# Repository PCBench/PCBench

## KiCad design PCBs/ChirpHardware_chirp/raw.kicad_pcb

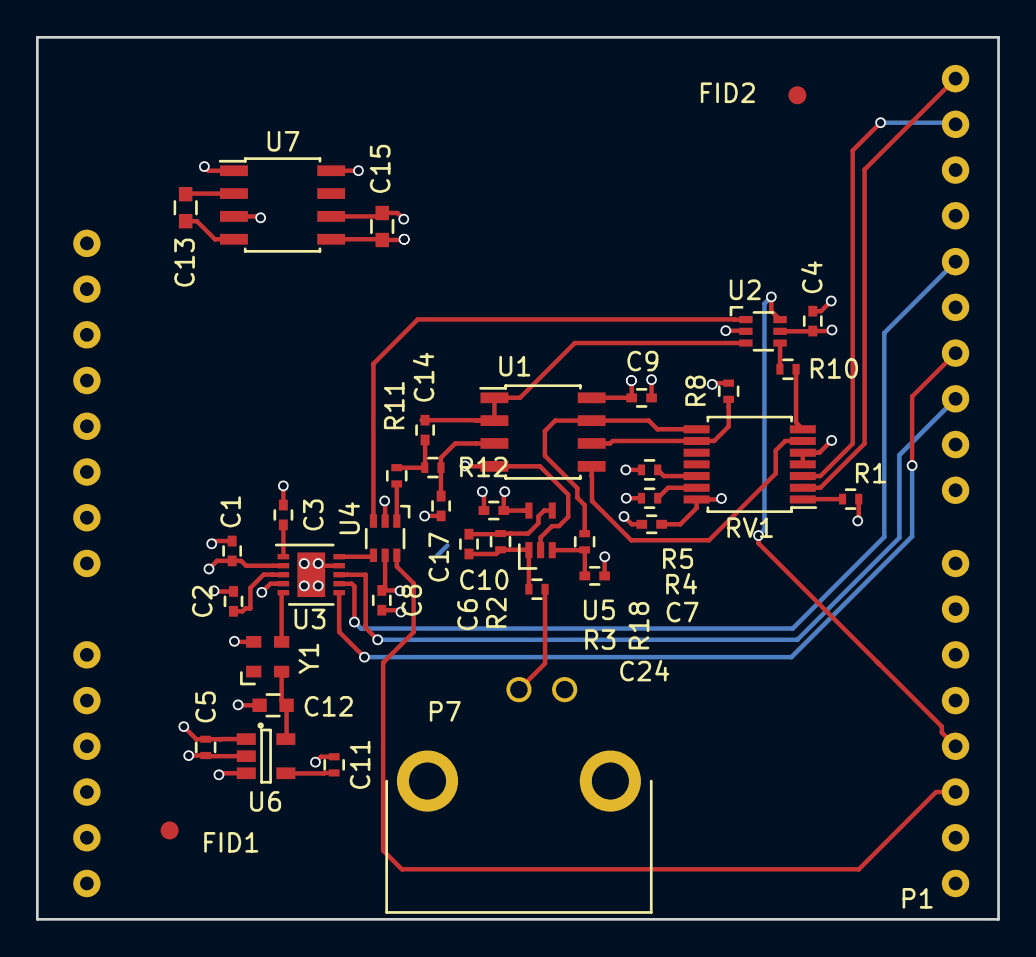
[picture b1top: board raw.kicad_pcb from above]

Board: 4 copper layers, 53.4 x 49.0 mm, 40 parts (0 on the bottom side), 35 nets.

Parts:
C1, C2, C3, C6, C14, C17, C24: C; C_0402
C4, C8, C9, C10: 0.01uF; C_0402
C5: 1uF; R_0402
C7: 0.1uF; C_0402
C11: 10nF; R_0402
C12: 2.2uF; C_0603
C13, C15: C; C_0603
FID1, FID2: Fiducial_1mm_Dia_2.54mm_Outer_CopperTop
P1: Arduino
P7: BNC; TE_BNC
R1, R4, R5: 0; R_0402
R2, R3, R11, R12, R18: R; R_0402
R8, R10: 2k; R_0402
RV1: MCP4651; TSSOP-14_4.4x5mm_Pitch0.65mm
U1: opa2335; SOIC-8_3.9x4.9mm_Pitch1.27mm
U2, U4: MUX; SC-70-6
U3: AD9837; DFN-10-1EP_3x3mm_Pitch0.5mm
U5: LMH6657; SOT23-5
U6: LP2985LV; SOT-23-5
U7: LM2660; SOIC-8_3.9x4.9mm_Pitch1.27mm
Y1: ASDMB-16MHZ; ADSM-16

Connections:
+5V: C1.1, C2.2, C3.1, C4.1, C5.1, C7.1, C8.1, C9.1, C10.1, P1.10, P1.13, P1.30, RV1.14, U1.8, U2.5, U3.2, U4.5, U5.5, U6.1, U6.3, U7.1, U7.8
Filter_IN: R11.2, U4.1
Filtered: C14.2, U1.1, U1.2, U2.3
GND: C1.2, C4.2, C5.2, C7.2, C8.2, C9.2, C10.2, C11.2, C12.2, C15.2, C17.2, C24.2, P1.8, P1.9, P1.29, P7.2, R1.2, R4.1, R5.1, R8.2, RV1.4, RV1.5, U2.2, U3.4, U3.9, U3.11, U4.2, U6.2, U7.3, U7.6, Y1.2
MOSI: P1.26, U3.6
unnamed: C2.1, U3.3
unnamed: C3.2, U3.1
unnamed: C6.1, R2.1, R3.2, U5.1
unnamed: C6.2, R2.2, U5.4
unnamed: C11.1, U6.4
unnamed: C12.1, U6.5, Y1.4
unnamed: C13.1, U7.2
unnamed: C13.2, U7.4
unnamed: C14.1, R11.1, R12.2
unnamed: C17.1, R12.1, U1.3
unnamed: C24.1, R18.1, U5.3
unnamed: P7.1, R3.1
unnamed: R1.1, RV1.1
unnamed: R4.2, RV1.13
unnamed: R5.2, RV1.12
unnamed: R8.1, RV1.9, U1.6
unnamed: R10.1, RV1.7
unnamed: R10.2, U2.4
unnamed: R18.2, RV1.8, U1.7
unnamed: RV1.6, U1.5
unnamed: U3.5, Y1.3
OUT: U3.10, U4.4
SCL: P1.32, RV1.2
SCLK: P1.28, U3.7
SDA: P1.31, RV1.3
SELECT_0: P1.17, U4.6
SELECT_1: P1.18, U2.6
SS: P1.25, U3.8
Square: U2.1, U4.3
VEE: C15.1, U1.4, U5.2, U7.5

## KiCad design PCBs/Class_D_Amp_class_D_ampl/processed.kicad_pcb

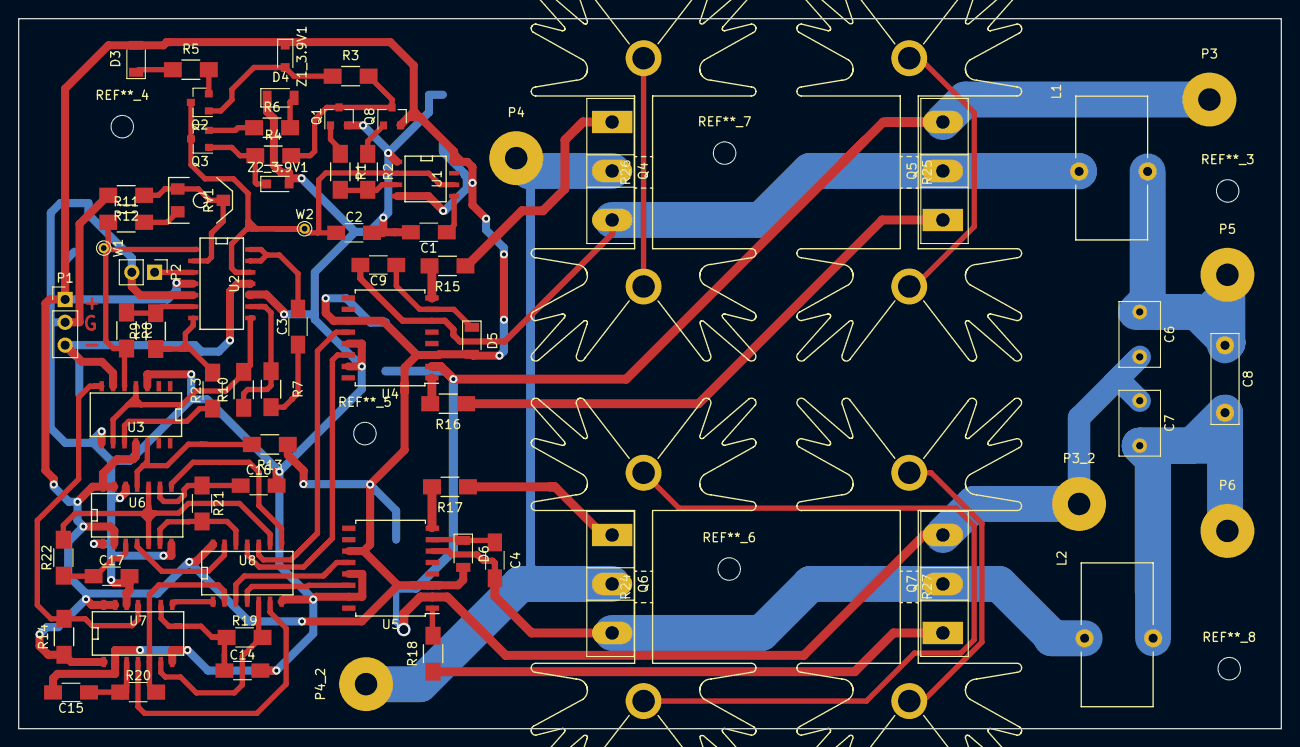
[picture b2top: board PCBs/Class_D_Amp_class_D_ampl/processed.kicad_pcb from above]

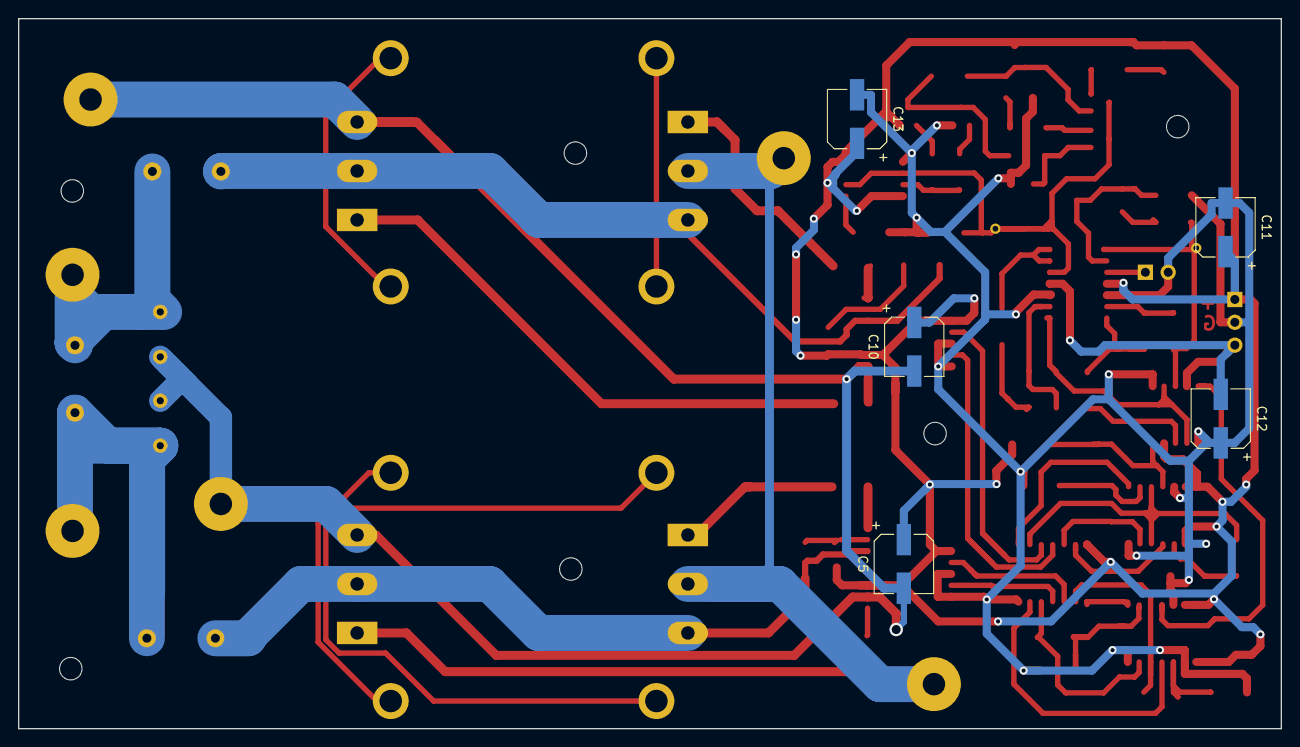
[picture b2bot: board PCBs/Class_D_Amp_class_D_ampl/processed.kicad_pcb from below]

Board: 2 copper layers, 140.5 x 79.0 mm, 79 parts (5 on the bottom side), 60 nets.

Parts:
C1, C2, C3: 10n; C_1206_HandSoldering
C4, C9: 100n; C_1206_HandSoldering
C5, C10: 47u; CP_Elec_6.3x5.8
C6, C7: 100p; C_Rect_L7.2mm_W4.5mm_P5.00mm_FKS2_FKP2_MKS2_MKP2
C8: 560p; C_Rect_L10.0mm_W3.0mm_P7.50mm_FKS3_FKP3
C11, C12, C13: 22u; CP_Elec_6.3x5.8
C14, C15, C16, C17: 100p; C_1206_HandSoldering
D3, D4, D5, D6: D; D_1206
L1, L2: 35u; Choke_Toroid_8x16mm_Vertical
P1: CONN_01X03; Pin_Header_Straight_1x03_Pitch2.54mm
P2: BNC; Pin_Header_Straight_1x02_Pitch2.54mm
P3, P3_2, P4, P4_2: CONN_01X01; SolderWirePad_single_2-5mmDrill
P5: CONN_speaker_plus; SolderWirePad_single_2-5mmDrill
P6: CONN_speaker_minus; SolderWirePad_single_2-5mmDrill
Q1, Q3: MMBT3904; SOT-23
Q2, Q8: MMBT3906; SOT-23
Q4, Q5, Q6, Q7: Q_NMOS_GDS; TO-247_TO-3P_Vertical
R1, R2: 4.7k; R_1206_HandSoldering
R3, R4: 100k; R_1206_HandSoldering
R5, R6: 4.7; R_1206_HandSoldering
R7, R10: 12k; R_1206_HandSoldering
R8, R9: 56k; R_1206_HandSoldering
R11, R23: 0; R_1206_HandSoldering
R12: NC; R_1206_HandSoldering
R13, R14: 1k2; R_1206_HandSoldering
R15, R16, R17, R18: 10; R_1206_HandSoldering
R19, R20, R21, R22: 3300; R_1206_HandSoldering
R24, R25, R26, R27: Heater; Heatsink_Fischer_SK129-STS_42x25mm_2xDrill2.5mm
RV1: POT; POT_SMD
U1: TLC555; SOIC-8-N
U2: TL084; SOIC-14_N
U3: LM319; SOIC-14_N
U4, U5: ir2010_SOIC; SOIC-16W_7.5x10.3mm_Pitch1.27mm
U6, U7: 40106; SOIC-14_N
U8: 14081; SOIC-14_N
W1, W2: TEST_1P; PINTST
Z1_3.9V1, Z2_3.9V1: DZ2J039; D_SOD-323_HandSoldering

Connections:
-12VA: C12.2, P1.3, U2.11, U3.6
/Mosfets and drivers/Hin_negative: U5.12, U8.3
/Mosfets and drivers/Hin_positive: U4.12, U8.10
/Mosfets and drivers/Lin_negative: U5.14, U8.4
/Mosfets and drivers/Lin_positive: U4.14, U8.11
/Operational Amplifiers/PWM_negative: R14.2, U3.7, U7.11
/Operational Amplifiers/PWM_positive: R13.2, U3.12, U6.11
/Operational Amplifiers/audio_in: P2.1, U2.3
/Operational Amplifiers/audio_inv: R23.1, U3.10
/Operational Amplifiers/audio_no_inv: R8.2, R11.1, U2.1, U3.5, W1.1
/Operational Amplifiers/triangular_filtered: R10.2, U2.8, U3.4, U3.9
/Operational Amplifiers/triangular_signal: C2.1, Q2.3, Q3.3, U1.2, U1.6, U2.12, W2.1
GND: C1.2, C2.2, C11.2, C12.1, C13.2, C14.2, C15.2, C16.2, C17.2, D4.1, P1.2, P2.2, Q1.2, R12.2, U1.1, U2.5, U2.10, U3.3, U3.8, U4.13, U4.15, U5.13, U5.15, U6.1, U6.7, U6.12, U7.2, U7.7, U7.12, U8.7, Z2_3.9V1.2
GNDPWR: C5.2, C6.2, C7.1, C10.2, P3.1, P3_2.1, Q5.3, Q7.3, U4.2, U5.2
unnamed: C1.1, U1.5
unnamed: C3.1, R7.2
unnamed: C3.2, U2.13, U2.14
unnamed: C4.1, D6.1, U5.7
unnamed: C4.2, L2.2, Q6.3, Q7.2, U5.6
unnamed: C6.1, C8.1, L1.1, P5.1
unnamed: C7.2, C8.2, L2.1, P6.1
unnamed: C9.1, D5.1, U4.7
unnamed: C9.2, L1.2, Q4.3, Q5.2, U4.6
unnamed: C14.1, R19.1, U7.9
unnamed: C15.1, R20.1, U7.3
unnamed: C16.1, R21.1, U6.9
unnamed: C17.1, R22.1, U6.3
unnamed: D3.1, R5.1
unnamed: D4.2, R6.2
unnamed: Q1.1, R1.1
unnamed: Q1.3, Q8.3, R3.2, R4.2
unnamed: Q2.1, R3.1, Z1_3.9V1.2
unnamed: Q2.2, R5.2
unnamed: Q3.1, R4.1, Z2_3.9V1.1
unnamed: Q3.2, R6.1
unnamed: Q4.1, R15.1
unnamed: Q5.1, R16.1
unnamed: Q6.1, R17.1
unnamed: Q7.1, R18.1
unnamed: Q8.1, R2.1
unnamed: R1.2, R2.2, U1.3
unnamed: R8.1, R9.2, U2.6
unnamed: R7.1, R10.1, U2.9
unnamed: R11.2, RV1.3
unnamed: R12.1, RV1.1, RV1.2, U2.2
unnamed: R15.2, U4.8
unnamed: R16.2, U4.1
unnamed: R17.2, U5.8
unnamed: R18.2, U5.1
unnamed: R19.2, U7.6, U8.5
unnamed: R20.2, U7.5, U7.10, U8.2
unnamed: R21.2, U6.6, U8.12
unnamed: R22.2, U6.5, U6.10, U8.9
unnamed: R9.1, R23.2, U2.7
unnamed: U6.4, U8.13
unnamed: U6.8, U8.8
unnamed: U7.4, U8.6
unnamed: U7.8, U8.1
VCC: C5.1, C10.1, C11.1, C13.1, D3.2, D5.2, D6.2, P1.1, Q8.2, R13.1, R14.1, U1.4, U1.8, U2.4, U3.11, U4.3, U4.11, U5.3, U5.11, U6.2, U6.13, U6.14, U7.1, U7.13, U7.14, U8.14, Z1_3.9V1.1
VEE: P4.1, P4_2.1, Q4.2, Q6.2

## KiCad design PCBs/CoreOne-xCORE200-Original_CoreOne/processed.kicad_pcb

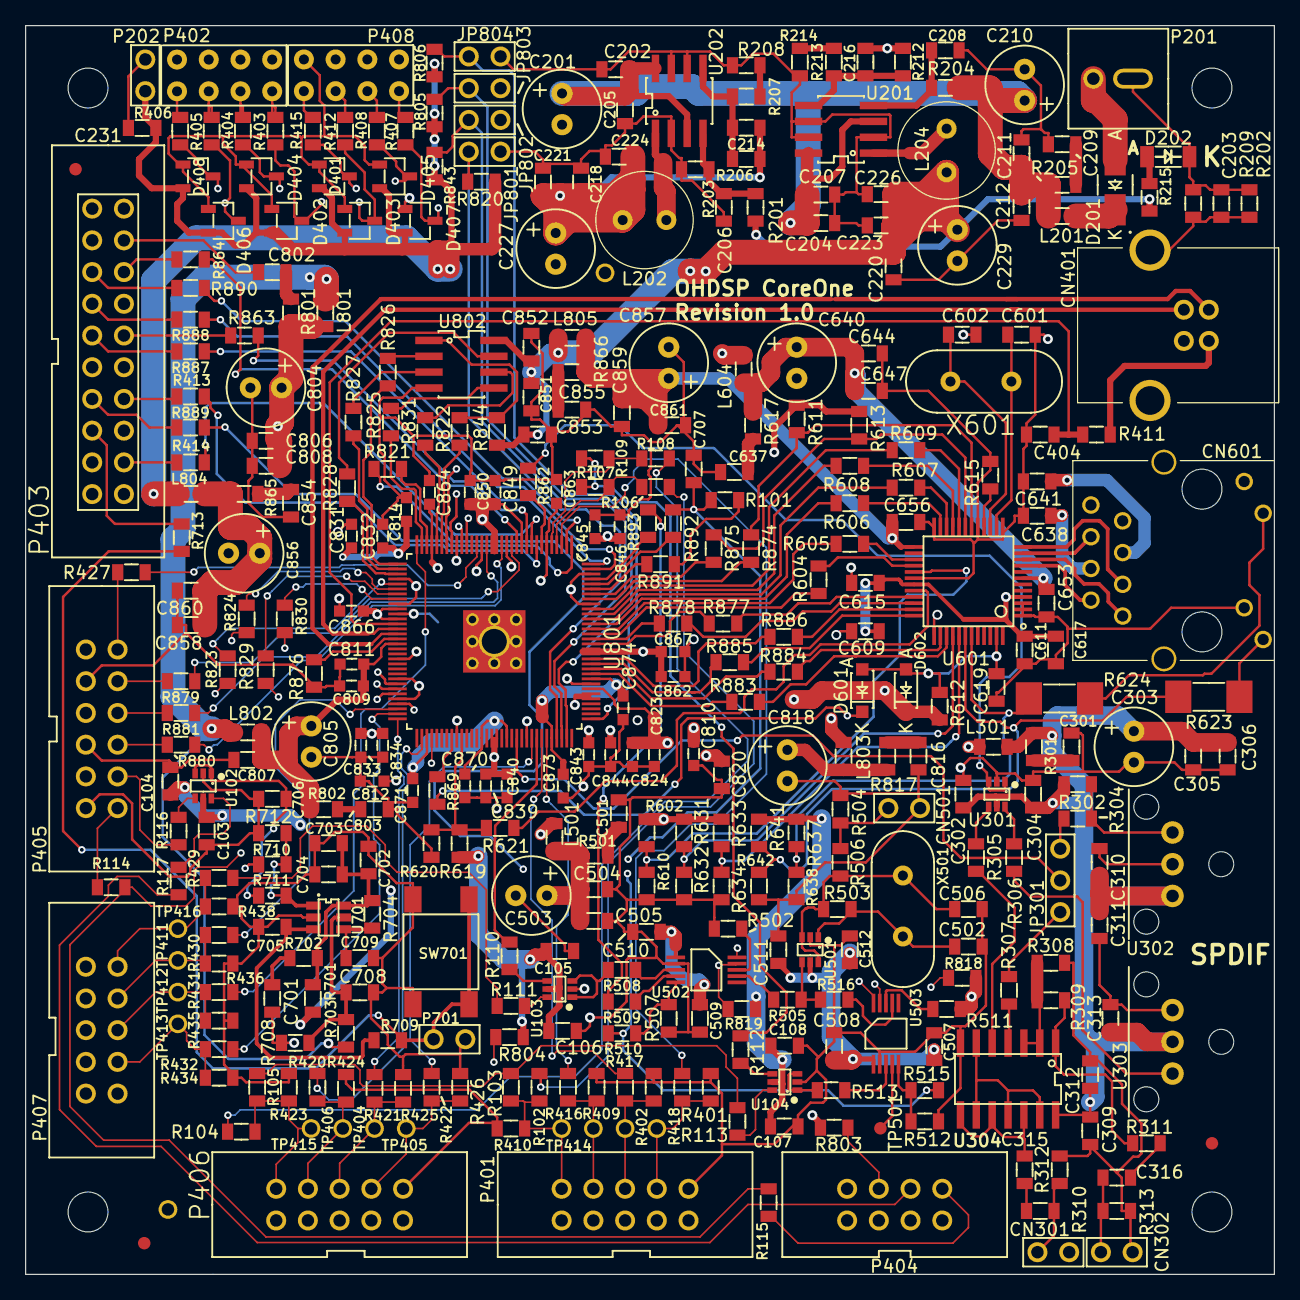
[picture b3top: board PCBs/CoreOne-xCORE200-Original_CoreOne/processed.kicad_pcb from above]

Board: 4 copper layers, 100.0 x 100.0 mm, 389 parts (1 on the bottom side), 245 nets.

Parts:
C103, C105, C107, C202, C204, C211, C218, C220, C221, C223, C305, C504, C644, C806, C807, C820, C858, C859: 22u; SMD-0805
C104, C106, C108, C203, C205, C206, C207, C208, C212, C224, C226, C231, C304, C306, C311, C312, C313, C315, C316, C404, C505, C508, C510, C512, C615, C617, C638, C641, C647, C653, C656, C703, C706, C707, C808, C852, C860, C861: 100n; SMD-0805
C201, C210, C227, C229, C303, C503, C640, C804, C805, C818, C856, C857: 220u; CAP-TH-D6.3mmP2.5mm
C209, C301, C501, C637, C701, C802, C803, C816, C854, C855: 100p; SMD-0805
C214, C216, C709: N/F; SMD-0805
C302, C309, C310, C507, C509, C511, C619, C702, C853: 10u; SMD-0805
C502, C506, C601, C602: 33p; SMD-0805
C609, C611: 1u; SMD-0805
C704, C705, C708, C851: 10n; SMD-0805
C809, C823, C831, C833, C839, C843, C845, C849, C862, C863, C864, C866, C870, C871, C873, C874: 100n; SMD-0603
C810, C812, C814: 1u; SMD-0603
C811, C824, C832, C834, C840, C844, C846, C850, C867: 10n; SMD-0603
CN301, CN302, CN501: COAX; CONN_SIL_2_1MM
CN401: CONN-USB-B-61729; CONN-USB-B-61729-0010
CN601: CONN_RJ45_ARJC02-111xxxx; CONN-RJ45-ARJC02-111xxxx
D201: B240A; DIODE-SMA
D202: Green LED 1206; SMD-1206
D401, D402, D403, D404, D405, D406, D407, D408: BAV99; IC-SOT23
D601, D602: SS14L; DIODE-SOD-123
FID201, FID202, FID203: MNT_HOLE; FID-1MM-3MM
JP301: CONN_3x1; CONN_SIL_3_1MM
JP801, JP802, JP803, JP804: CONN_2x1; CONN_SIL_2_1MM
L201, L301, L501, L604, L801, L802, L803, L804, L805: 600R@100MHz; SMD-0805
L202: DR0608-332L; IND-TH-DR0608
L204: DR0608-153L; IND-TH-DR0608
MNT201, MNT202, MNT203, MNT204: MNT_HOLE; MNT_HOLE_3.2mm
P201: CONN_2x1; CONN-2WAY-2.54mm-3.81mm-SPACING
P202, P701: CONN_2x1; CONN_SIL_2_1MM
P401, P406, P407: CONN_02X05; CONN_DIL_2X5_BOX_1MM
P402, P408: CONN_02X04; CONN_DIL_2X04
P403: CONN_02X10; CONN_DIL_2X10_BOX_1MM
P404: CONN_02X04; CONN_DIL_2X4_BOX_1MM
P405: CONN_02X06; CONN_DIL_2X6_BOX_1MM
R101, R102, R104, R106, R108, R208, R214, R413, R414, R416, R417, R418, R420, R421, R422, R427, R429, R713, R821, R822, R823, R824, R825, R826, R827, R828, R829, R830, R831, R862, R874, R875, R887, R888, R890, R891, R892, R893: 0; SMD-0805
R103, R105, R107, R109, R401, R402, R409, R410, R423, R424, R425, R426, R434, R435, R436, R438, R504, R506, R510, R515, R602, R620, R631, R633, R638, R642, R803, R804: N/F; SMD-0805
R110, R111, R112, R113, R114, R115, R116, R117, R604, R605, R606, R607, R608, R609, R621, R863, R864, R869, R877, R878, R879, R880, R881, R883, R884, R885, R886, R889: 33; SMD-0805
R201, R204, R403, R404, R405, R406, R407, R408, R412, R415, R502, R511, R610, R611, R613, R619, R632, R634, R805, R806, R820, R843: 1k; SMD-0805
R202, R209: 10; SMD-0805
R203: 750; SMD-0805
R205, R301, R501, R617, R702, R801, R802, R817, R865, R866: 47; SMD-0805
R206: 8k25; SMD-0805
R207: 33k; SMD-0805
R212: 36k; SMD-0805
R213: 11k5; SMD-0805
R215: 220; SMD-0805
R302, R308, R309, R612, R703, R844: 10k; SMD-0805
R304, R305, R306, R307, R313, R430, R431, R432: 75; SMD-0805
R310: 360; SMD-0805
R311, R709, R710, R711: 100; SMD-0805
R312: 91; SMD-0805
R411, R701: 1; SMD-0805
R503: 1Meg; SMD-0805
R505, R508, R509, R513, R516: 33R; SMD-0805
R507, R512: 0R; SMD-0805
R615: 6K49; SMD-0805
R623, R624: 220; SMD_MELF_0207
R637, R641: 4k7; SMD-0805
R704, R712: 100k; SMD-0805
R708: 7k5; SMD-0805
R818, R819: 2k2; SMD-0805
R876: 43R2; SMD-0805
SW701: SWITCH; SW_TACT_SMD
TP401, TP402, TP403, TP404, TP405, TP406, TP407, TP408, TP411, TP412, TP413, TP414, TP415, TP416: PIN; TP-TH-1mm
TP501, TP803: PIN; TP-1mm
U102, U103, U104, U301: NC7WZ16P6X; IC-SC70-6
U201, U202: IC-REG-ST1S40IDR; IC_SOIC_8
U302: IC-SPDIF-RX-OPTO; IC_SPDIF_OPTO
U303: IC-SPDIF-TX-OPTO; IC_SPDIF_OPTO
U304: 74HC04; IC_SOIC_14
U501: NC7WZ04P6X; IC-SC70-6
U502: CS2200-CP; IC-MSOP-10
U503: CS2100-CP; IC-MSOP-10
U601: KSZ8081MLX; IC-LQFP48_7x7
U701: TPS3808; IC-SOT23-6
U801: IC-uC-XE216-512-TQ128; IC-TQ128-XMOS-HF
U802: IC-FLASH-SPI; IC_SOIC_8
X501: 24M000; XTAL_HC49_TH
X601: 25M000; XTAL_HC49_TH

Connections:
+1V0: C214.1, C218.1, C221.1, C224.1, C227.1, L202.2, L801.1, L802.1, L803.1, R206.2, R703.1
+3V3: C103.1, C104.1, C105.1, C106.1, C107.1, C108.1, C216.1, C220.1, C223.1, C226.1, C229.1, C231.1, C851.1, C852.1, C853.1, D401.2, D402.2, D403.2, D404.2, D405.2, D406.2, D407.2, D408.2, D602.2, L204.2, L301.1, L501.1, L604.1, L804.1, L805.1, P202.1, R201.2, R212.2, R215.1, R511.1, R602.1, R611.1, R612.1, R613.1, R619.1, R631.1, R633.1, R637.1, R641.1, R701.2, R803.1, R804.1, R805.1, R806.1, R818.1, R819.1, R820.1, R843.1, R844.1, U102.5, U103.5, U104.5, U802.8
/AUD_CLK1: R508.1, U103.1, U103.3
/AUD_CLK2: R513.1, U104.1, U104.3
/AUD_MCLK1A: R110.1, U801.89
/AUD_MCLK1B: R111.1, R429.1
/AUD_MCLK2A: R107.1, R109.1, R112.1
/AUD_MCLK2B: R103.1, R105.1, R113.1
/AUD_MUTE: R114.2, R115.2, U801.68
/AUD_PLLSYNC: R510.1, R515.1, R821.1
/AUX_DIGI0: D402.3, R403.2, U801.57
/AUX_DIGI1: D404.3, R404.2, U801.58
/AUX_DIGI2: D406.3, R405.2, U801.59
/AUX_DIGI3: D408.3, R406.2, U801.61
/AUX_DIGI4: D407.3, R407.2, U801.22
/AUX_DIGI5: D405.3, R408.2, U801.23
/AUX_DIGI6: D403.3, R412.2, U801.25
/AUX_DIGI7: D401.3, R415.2, U801.26
/Clock-CS2200/24M_CLK_1: R505.1, U502.7
/Clock-CS2200/24M_CLK_2: R516.1, U503.7
/Clock-CS2200/CS_3V3: C503.1, C504.1, C505.1, C507.1, C508.1, C509.1, C510.1, C511.1, C512.1, L501.2, R501.1, U501.5, U502.1, U503.1
/Connectors/I2S_MCLKB/D4: P406.2, R104.2, R105.2, R423.2, TP415.1
/Connectors/I2S_MCLKC/D3: P401.2, R102.2, R103.2, R410.2, TP414.1
/ETH_INT: R619.2, R620.1, R621.1, U801.74
/ETH_MDC: R613.2, R875.2, U601.19
/ETH_MDIO: R611.2, R874.2, U601.18
/ETH_RST: D601.2, R869.2
/ETH_RX0: R606.2, U801.116
/ETH_RX1: R607.2, U801.117
/ETH_RX2: R608.2, U801.118
/ETH_RX3: R609.2, U801.119
/ETH_RX_CLK: R604.2, U801.114
/ETH_RX_CTL: R605.2, U801.115
/ETH_TX0: R886.2, U601.35
/ETH_TX1: R885.2, U601.36
/ETH_TX2: R884.2, U601.38
/ETH_TX3: R883.2, U601.39
/ETH_TX_CLK: R877.2, U601.33
/ETH_TX_CTL: R878.2, U601.34
/Eth-KSZ8081/A3V3: C640.1, C644.1, C647.1, C653.1, L604.2, R617.1, U601.7
/Eth-KSZ8081/CONFIG0: R631.2, R632.1, U601.40
/Eth-KSZ8081/CONFIG1: R633.2, R634.1, U601.41
/Eth-KSZ8081/D1V2: C609.1, C611.1, C615.1, C617.1, U601.4, U601.31
/Eth-KSZ8081/ISO: R602.2, R610.1, U601.29
/Eth-KSZ8081/KSZ_RST: C619.1, D601.1, D602.1, R612.2, U601.47
/Eth-KSZ8081/NWAYEN: R623.2, R641.2, R642.1, U601.42
/Eth-KSZ8081/RX_N: CN601.2, U601.9
/Eth-KSZ8081/RX_P: CN601.1, U601.10
/Eth-KSZ8081/SPEED: R624.2, R637.2, R638.1, U601.43
/Eth-KSZ8081/TX_N: CN601.6, U601.11
/Eth-KSZ8081/TX_P: CN601.3, U601.12
/GEN_RST: C706.1, R711.1, U102.1, U102.3
/I2C1_SCL: R819.2, R823.1, U502.9, U503.9
/I2C1_SDA: R818.2, R824.1, U502.10, U503.10
/I2C2_SCL: P404.4, R803.2, R830.1
/I2C2_SDA: P404.2, R804.2, R829.1
/I2C_MUTE: P404.8, R115.1
/I2C_RST: P404.6, R117.1
/I2S_BCLK0: R431.1, U801.32
/I2S_BCLK1: R421.2, U801.64
/I2S_BCLK2: R417.2, U801.90
/I2S_D3: R102.1, R106.1
/I2S_D4: R104.1, R108.1
/I2S_LRCLK0: R430.1, U801.62
/I2S_LRCLK1: R420.2, U801.66
/I2S_LRCLK2: R416.2, U801.91
/I2S_SDATA0: R432.1, U801.63
/I2S_SDATA1: R422.2, U801.88
/I2S_SDATA2: R418.2, U801.3
/SPDIF_RX: JP301.2, U801.85
/SPDIF_TX: R862.1, U301.1, U301.3
/SPI_CS1: P405.8, R880.2
/SPI_MISO: R427.2, U801.20
/SPI_MOSI: P405.6, R881.2
/SPI_MUTE: P405.12, R114.1
/SPI_RST: P405.10, R116.1
/SPI_SCLK: P405.4, R879.2
/SYS_CLK: R509.1, R893.2
/TCK: P403.9, R887.2
/TDI: P403.5, R890.2
/TDO: P403.13, R889.2
/TMS: P403.7, R888.2
/USBD_N: CN401.2, U801.47
/USBD_P: CN401.3, U801.46
/USB_VBUS: C404.2, R411.2, U801.45
/XL_DN0: R413.2, U801.8
/XL_DN1: R414.2, U801.9
/XL_UP0: P403.10, R863.1
/XL_UP1: P403.6, R864.1
/XMOS200/AUD_MCLKB/I2S_DATA3: R106.2, R107.2, U801.4
/XMOS200/AUD_MCLKC/I2S_DATA4: R108.2, R109.2, U801.5
/XMOS200/DVDD: C804.1, C806.1, C808.1, C810.1, C812.1, C814.1, C831.1, C832.1, C833.1, C834.1, C839.1, C840.1, C843.1, C844.1, C845.1, C846.1, C849.1, C850.1, L801.2, R801.1, U801.11, U801.16, U801.17, U801.24, U801.36, U801.41, U801.56, U801.60, U801.73, U801.80, U801.81, U801.87, U801.101, U801.102, U801.120, U801.126
/XMOS200/IOVDD: C856.1, C858.1, C860.1, C863.1, C864.1, C866.1, C870.1, C871.1, C873.1, C874.1, L804.2, R865.1, U801.6, U801.14, U801.19, U801.29, U801.42, U801.44, U801.52, U801.67, U801.78, U801.83, U801.92, U801.105
/XMOS200/MEM_SPI_CLK: R831.1, U802.6
/XMOS200/MEM_SPI_CS: R822.1, R844.2, U802.1
/XMOS200/MEM_SPI_D0: R825.1, U802.5
/XMOS200/MEM_SPI_D1: R826.1, U802.2
/XMOS200/MEM_SPI_D2: R827.1, U802.3
/XMOS200/MEM_SPI_D3: R828.1, U802.7
/XMOS200/MODE1: JP801.1, R820.2, U801.93
/XMOS200/MODE2: JP802.1, R843.2, U801.94
/XMOS200/MODE3: JP803.1, R805.2, U801.95
/XMOS200/MODE4: JP804.1, R806.2, U801.97
/XMOS200/PLL_VDD: C818.1, C820.1, C823.1, C824.1, L803.2, R817.1, U801.103
/XMOS200/USB_VDD: C805.1, C807.1, C809.1, C811.1, L802.2, R802.1, U801.49
/XMOS200/~TRST~: R101.1, R891.2
/XMOS_RST: C707.1, R101.2, R710.1, R892.2
/XSYS_RST: P403.15, R713.2
GNDD: C103.2, C104.2, C105.2, C106.2, C107.2, C108.2, C201.2, C202.1, C203.1, C204.1, C205.1, C206.1, C207.1, C208.1, C209.2, C210.2, C211.1, C212.1, C218.2, C220.2, C221.2, C223.2, C224.2, C226.2, C227.2, C229.2, C231.2, C301.2, C302.2, C303.2, C304.2, C305.2, C306.2, C309.2, C310.2, C311.2, C312.2, C313.2, C404.1, C501.2, C502.2, C503.2, C504.2, C505.2, C506.2, C507.2, C508.2, C509.2, C510.2, C511.2, C512.2, C601.2, C602.2, C609.2, C611.2, C615.2, C617.2, C619.2, C637.2, C638.2, C640.2, C641.2, C644.2, C647.2, C653.2, C656.2, C701.2, C702.2, C703.2, C704.2, C705.2, C706.2, C707.2, C708.2, C709.2, C802.2, C803.2, C804.2, C805.2, C806.2, C807.2, C808.2, C809.2, C810.2, C811.2, C812.2, C814.2, C816.2, C818.2, C820.2, C823.2, C824.2, C831.2, C832.2, C833.2, C834.2, C839.2, C840.2, C843.2, C844.2, C845.2, C846.2, C849.2, C850.2, C851.2, C852.2, C853.2, C854.2, C855.2, C856.2, C857.2, C858.2, C859.2, C860.2, C861.2, C862.2, C863.2, C864.2, C866.2, C867.2, C870.2, C871.2, C873.2, C874.2, CN301.2, CN302.2, CN401.4, CN501.2, CN601.10, CN601.12, D202.2, D401.1, D402.1, D403.1, D404.1, D405.1, D406.1, D407.1, D408.1, JP801.2, JP802.2, JP803.2, JP804.2, P201.2, P202.2, P401.1, P401.3, P401.5, P401.7, P401.9, P401.10, P402.1, P402.3, P402.5, P402.7, P403.4, P403.8, P403.12, P403.16, P403.20, P404.1, P404.3, P404.5, P404.7, P405.1, P405.3, P405.5, P405.7, P405.9, P405.11, P406.1, P406.3, P406.5, P406.7, P406.9, P406.10, P407.1, P407.3, P407.5, P407.7, P407.9, P407.10, P408.1, P408.3, P408.5, P408.7, P701.2, R202.2, R203.1, R208.1, R209.2, R214.1, R308.1, R312.1, R313.1, R401.1, R402.1, R409.1, R410.1, R423.1, R424.1, R425.1, R426.1, R434.1, R435.1, R436.1, R438.1, R502.2, R504.1, R507.2, R512.2, R610.2, R615.2, R620.2, R632.2, R634.2, R638.2, R642.2, R708.1, R712.1, R876.1, SW701.2, TP407.1, TP408.1, U102.2, U103.2, U104.2, U201.2, U201.6, U201.7, U202.2, U202.6, U202.7, U301.2, U302.2, U303.3, U304.7, U501.2, U502.2, U503.2, U601.1, U601.2, U601.3, U601.13, U601.17, U601.24, U601.30, U601.37, U701.2, U801.104, U801.EP, U802.4
GNDPWR: C203.2, CN401.5, CN601.8, CN601.13, R202.1, R209.1
unnamed: C206.2, R201.1, R203.2, U202.4
unnamed: C208.2, R204.1, U201.4
unnamed: C209.1, R205.2
unnamed: C214.2, R206.1, R207.2, U202.5
unnamed: C216.2, R212.1, R213.2, U201.5
unnamed: C301.1, R301.2
unnamed: C302.1, C303.1, C304.1, C305.1, C306.1, C309.1, C310.1, C311.1, C312.1, C313.1, L301.2, R301.1, R302.1, U301.5, U302.1, U303.2, U304.14
unnamed: C315.1, R310.2
unnamed: C315.2, U304.8, U304.10, U304.12
unnamed: C316.1, R311.2
unnamed: C316.2, CN302.1, R313.2
unnamed: C501.1, R501.2
unnamed: C502.1, R503.2, U501.1, X501.1
unnamed: C506.1, R503.1, R506.2, U501.3, U501.6, X501.2
unnamed: C601.1, U601.14, X601.1
unnamed: C602.1, U601.15, X601.2
unnamed: C637.1, R617.2
unnamed: C638.1, CN601.4
unnamed: C641.1, CN601.5
unnamed: C701.1, R702.2
unnamed: C702.1, C703.1, C704.1, R701.1, R702.1, R704.1, U701.6
unnamed: C705.1, R709.1, U701.3
unnamed: C708.1, R703.2, R708.2, U701.5
unnamed: C709.1, R704.2, U701.4
unnamed: C802.1, R801.2
unnamed: C803.1, R802.2
unnamed: C816.1, R817.2
unnamed: C854.1, R865.2
unnamed: C855.1, R866.2
unnamed: CN301.1, R310.1, R312.2
unnamed: CN401.1, R411.1
unnamed: CN501.1, R504.2, R506.1
unnamed: CN601.9, R623.1
unnamed: CN601.11, R624.1
unnamed: D201.1, P201.1
unnamed: D201.2, L201.1
unnamed: D202.1, R215.2
unnamed: JP301.1, R304.1
unnamed: JP301.3, R307.2
unnamed: L202.1, U202.1
unnamed: L204.1, U201.1
unnamed: P401.4, R409.2, R416.1, TP401.1
unnamed: P401.6, R402.2, R417.1, TP402.1
unnamed: P401.8, R401.2, R418.1, TP403.1
unnamed: P402.2, R403.1
unnamed: P402.4, R404.1
unnamed: P402.6, R405.1
unnamed: P402.8, R406.1
unnamed: P403.14, R413.1
unnamed: P403.18, R414.1
unnamed: P405.2, R427.1
unnamed: P406.4, R420.1, R424.2, TP406.1
unnamed: P406.6, R421.1, R425.2, TP404.1
unnamed: P406.8, R422.1, R426.2, TP405.1
unnamed: P407.2, R429.2, R438.2, TP416.1
unnamed: P407.4, R430.2, R436.2, TP411.1
unnamed: P407.6, R431.2, R435.2, TP412.1
unnamed: P407.8, R432.2, R434.2, TP413.1
unnamed: P408.2, R407.1
unnamed: P408.4, R408.1
unnamed: P408.6, R412.1
unnamed: P408.8, R415.1
unnamed: P701.1, R709.2, R713.1, SW701.1
unnamed: R110.2, U103.4
unnamed: R111.2, U103.6
unnamed: R112.2, U104.4
unnamed: R113.2, U104.6
unnamed: R116.2, U102.4
unnamed: R117.2, U102.6
unnamed: R207.1, R208.2
unnamed: R213.1, R214.2
unnamed: R302.2, R304.2, U302.3
unnamed: R305.1, U304.5
unnamed: R305.2, U301.4
unnamed: R306.1, U301.6
unnamed: R306.2, U303.1
unnamed: R307.1, U304.4
unnamed: R308.2, R309.1, U304.2, U304.3
unnamed: R309.2, R311.1, U304.1
unnamed: R502.1, U502.8
unnamed: R505.2, R516.2, U501.4
unnamed: R507.1, R510.2, U502.5
unnamed: R508.2, U502.3
unnamed: R509.2, U502.4
unnamed: R511.2, U503.8
unnamed: R512.1, R515.2, U503.5
unnamed: R513.2, U503.3
unnamed: R604.1, U601.28
unnamed: R605.1, U601.27
unnamed: R606.1, U601.23
unnamed: R607.1, U601.22
unnamed: R608.1, U601.21
unnamed: R609.1, U601.20
unnamed: R615.1, U601.16
unnamed: R621.2, U601.32
unnamed: R710.2, R711.2, R712.2, U701.1
unnamed: R821.2, U801.30
unnamed: R822.2, U801.27
unnamed: R823.2, U801.37
unnamed: R824.2, U801.38
unnamed: R825.2, U801.31
unnamed: R826.2, U801.33
unnamed: R827.2, U801.34
unnamed: R828.2, U801.35
unnamed: R829.2, U801.39
unnamed: R830.2, U801.40
unnamed: R831.2, U801.28
unnamed: R862.2, U801.7
unnamed: R863.2, U801.10
unnamed: R864.2, U801.12
unnamed: R869.1, U801.72
unnamed: R874.1, U801.121
unnamed: R875.1, U801.122
unnamed: R876.2, U801.48
unnamed: R877.1, U801.112
unnamed: R878.1, U801.113
unnamed: R879.1, U801.13
unnamed: R880.1, U801.15
unnamed: R881.1, U801.18
unnamed: R883.1, U801.106
unnamed: R884.1, U801.107
unnamed: R885.1, U801.108
unnamed: R886.1, U801.109
unnamed: R887.1, U801.128
unnamed: R888.1, U801.127
unnamed: R889.1, U801.1
unnamed: R890.1, U801.2
unnamed: R891.1, U801.123
unnamed: R892.1, U801.124
unnamed: R893.1, U801.125
unnamed: TP501.1, U503.4
unnamed: TP803.1, U801.43
unnamed: U304.6, U304.9, U304.11, U304.13
VCC: C201.1, C202.2, C204.2, C205.2, C207.2, C210.1, C211.2, C212.2, L201.2, R204.2, R205.1, U201.3, U201.8, U202.3, U202.8
VDD: C656.1, C857.1, C859.1, C861.1, C862.1, C867.1, L805.2, R866.1, U601.25, U801.110, U801.111

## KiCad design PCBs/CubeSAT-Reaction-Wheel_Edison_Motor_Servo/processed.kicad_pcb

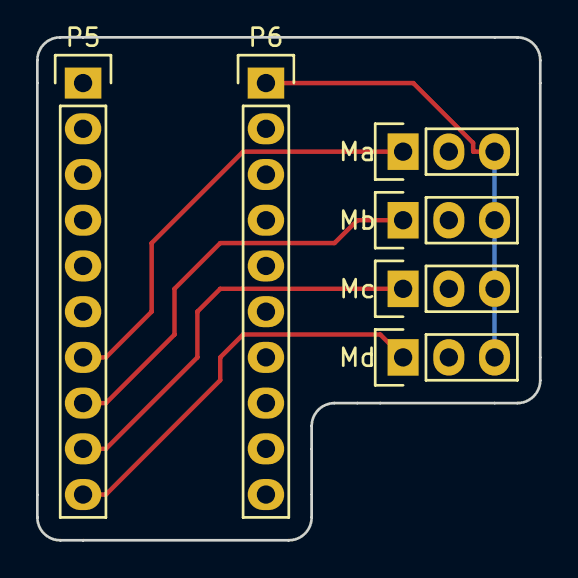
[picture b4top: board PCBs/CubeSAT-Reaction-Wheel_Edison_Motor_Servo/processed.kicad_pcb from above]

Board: 2 copper layers, 27.9 x 27.9 mm, 6 parts (0 on the bottom side), 5 nets.

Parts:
Ma: CONN_01X03; Socket_Strip_Straight_1x03
Mb: CONN_01X03; Socket_Strip_Straight_1x03
Mc: CONN_01X03; Socket_Strip_Straight_1x03
Md: CONN_01X03; Socket_Strip_Straight_1x03
P5, P6: CONN_01X10; Socket_Strip_Straight_1x10

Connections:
GND: Ma.3, Mb.3, Mc.3, Md.3, P6.1
unnamed: Ma.1, P5.7
unnamed: Mb.1, P5.8
unnamed: Mc.1, P5.9
unnamed: Md.1, P5.10

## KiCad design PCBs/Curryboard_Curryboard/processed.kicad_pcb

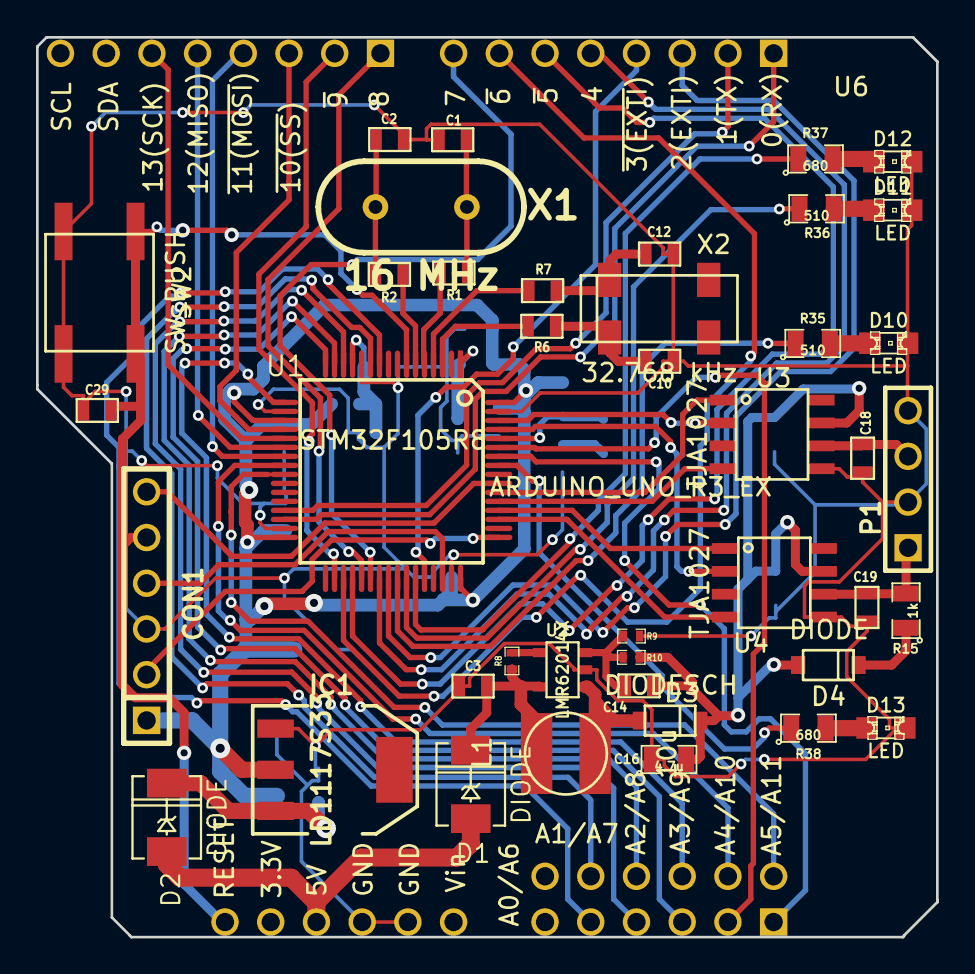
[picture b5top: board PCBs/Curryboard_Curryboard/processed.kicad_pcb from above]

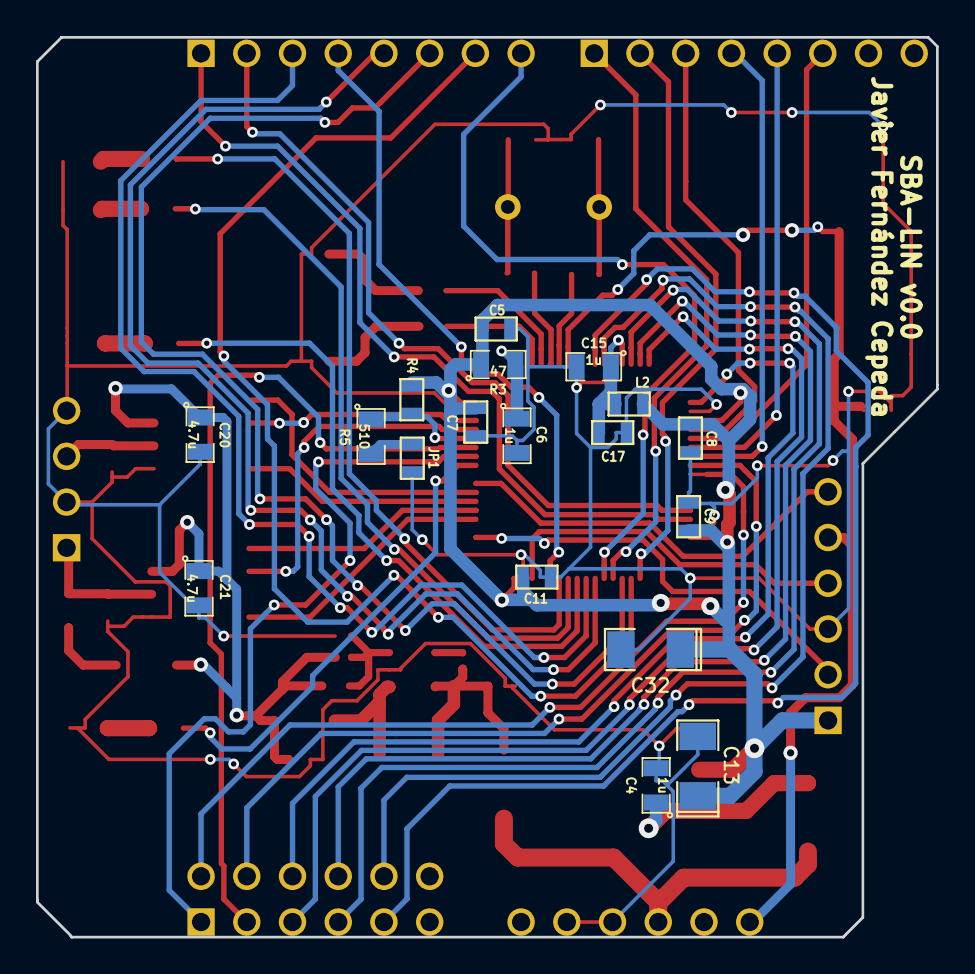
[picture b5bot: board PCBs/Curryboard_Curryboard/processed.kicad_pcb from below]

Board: 2 copper layers, 50.0 x 50.0 mm, 60 parts (18 on the bottom side), 66 nets.

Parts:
C1, C2: 4.7p; SM0603
C3: 3.3u; SM0603
C4, C6, C15: 1u; SM0805
C5, C7, C8, C9, C11, C17, C29: 100n; SM0603
C10, C12: 6.8p; SM0603
C13: 10u; SM1206POL
C14: 330p; SM0603
C16, C20, C21: 4.7u; SM0805
C18: 220p; SM0603
C19: 1n; SM0603
C32: 4u7; SM1206POL
CON1: SWD; PIN_ARRAY-6X1
D1, D2: DIODE; DO-214AC(SMA)
D3: DIODESCH; SOD123
D4: DIODE; SOD123
D10, D11, D12, D13: LED; LED-0805
IC1: LD1117S33; SOT223
JP1: JUMPER; SM0603
L1: 10u; 74477310
L2: fcm1608; SM0603
P1: CONN_4; PIN_ARRAY_4x1
R1, R2, R6, R7: 0; SM0603
R3: 47; SM0805
R4: 10k; SM0603
R5, R35, R36: 510; SM0805
R8: 1000k; SM0402
R9: 976; SM0402
R10: 8.66k; SM0402
R15: 1k; SM0805
R37, R38: 680; SM0805
SW2: SW_PUSH; EVQP0
U1: STM32F105R8; LQFP64
U2: LMR62014X; SOT23-5
U3, U4: TJA1027; SOIC8
U6: ARDUINO_UNO_R3_EX; ArduinoUNOShieldR3EX
X1: 16 MHz; HC-49V
X2: 32.768 kHz; RTC

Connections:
/LIN Interface/EN_LIN1: U1.61, U4.2
/LIN Interface/EN_LIN2: U1.62, U3.2
/LIN Interface/LIN1: C19.1, P1.1, R15.2, U4.6
/LIN Interface/LIN2: C18.1, P1.3, U3.6
/LIN Interface/RX_LIN1: U1.52, U4.1
/LIN Interface/RX_LIN2: U1.54, U3.1
/LIN Interface/TX_LIN1: U1.51, U4.4
/LIN Interface/TX_LIN2: U1.53, U3.4
/OSC32_IN: R6.2, U1.3
/OSC32_OUT: R7.2, U1.4
/OSC_IN: R1.2, U1.5
/OSC_OUT: R2.2, U1.6
/Peripherals/5V: D1.1, D2.1, U6.22
/Peripherals/A1: U1.10, U6.18
/Peripherals/A2: U1.14, U6.17
/Peripherals/A3: U1.16, U6.16
/Peripherals/A7: U1.11, U6.29
/Peripherals/A8: U1.15, U6.30
/Peripherals/A9: U1.17, U6.31
/Peripherals/A10: U1.24, U6.32
/Peripherals/A11: U1.25, U6.33
/Peripherals/GPIO1: U1.37, U6.8
/Peripherals/GPIO2: U1.38, U6.7
/Peripherals/GPIO3: U1.39, U6.4
/Peripherals/GPIO4: U1.40, U6.2
/Peripherals/LED1: R35.1, U1.41
/Peripherals/LED2: R36.1, U1.42
/Peripherals/LED3: R37.1, U1.43
/Peripherals/LED4: R38.1, U1.57
/Peripherals/PWM1: U1.34, U6.9
/Peripherals/PWM2: U1.35, U6.6
/Peripherals/PWM3: U1.36, U6.5
/Peripherals/PWM4: U1.44, U6.3
/Peripherals/RESET_BUTTON: C29.1, CON1.5, SW2.1, U1.7, U6.24
/Peripherals/RX: U1.30, U6.0
/Peripherals/SCL: U1.58, U6.14
/Peripherals/SDA: U1.59, U6.15
/Peripherals/SPI_MISO: U1.22, U6.12
/Peripherals/SPI_MOSI: U1.23, U6.11
/Peripherals/SPI_NSS: U1.20, U6.10
/Peripherals/SPI_SCLK: U1.21, U6.13
/Peripherals/TX: U1.29, U6.1
/Power Interface/3V3: C5.1, C7.2, C8.2, C9.2, C11.2, C13.1, C32.1, CON1.1, IC1.2, L2.1, R3.1, R4.1, U1.19, U1.32, U1.48, U1.64
/Power Interface/12V: C14.2, C16.2, C20.1, C21.1, D3.2, D4.1, R10.2, U3.7, U4.7
/Power Interface/VDDA: C15.1, C17.1, L2.2, U1.13
/SWCLK: CON1.2, U1.49
/SWDIO: CON1.4, U1.46
/SWO: CON1.6, U1.55
GND: C1.1, C2.1, C3.2, C4.2, C5.2, C6.2, C7.1, C8.1, C9.1, C10.1, C11.1, C12.1, C13.2, C15.2, C16.1, C17.2, C18.2, C19.2, C20.2, C21.2, C29.2, C32.2, CON1.3, D10.2, D11.2, D12.2, D13.2, IC1.1, JP1.2, P1.2, P1.4, R9.2, SW2.2, U1.12, U1.18, U1.31, U1.47, U1.63, U2.2, U3.5, U4.5, U6.21, U6.25
unnamed: JP1.1, R5.2
unnamed: C6.1, R3.2, U1.1
unnamed: R4.2, R5.1, U1.60
unnamed: C1.2, R1.1, X1.2
unnamed: C2.2, R2.1, X1.1
unnamed: C10.2, R6.1, X2.2
unnamed: C12.2, R7.1, X2.1
unnamed: D11.1, R36.2
unnamed: D10.1, R35.2
unnamed: D13.1, R38.2
unnamed: D12.1, R37.2
unnamed: D4.2, R15.1
unnamed: C3.1, D1.2, L1.1, R8.1, U2.5
unnamed: R8.2, U2.4
unnamed: C14.1, R9.1, R10.1, U2.3
unnamed: C4.1, D2.2, IC1.3
unnamed: D3.1, L1.2, U2.1

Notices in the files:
PCBs/CoreOne-xCORE200-Original_CoreOne/processed.kicad_pcb:
Licensed under the TAPR Open Hardware License (www.tapr.org/OHL). This documentation
Copyright Paul Janicki 2017
Copyright ©
Licensed under TAPR OHL
